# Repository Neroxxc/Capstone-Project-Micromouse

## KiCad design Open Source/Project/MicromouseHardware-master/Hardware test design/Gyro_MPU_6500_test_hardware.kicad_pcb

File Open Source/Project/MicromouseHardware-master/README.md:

# MicromouseHardware
This is the Hardware design for my micromouse. I will be participating in the UC San Diego's IEEE Micromouse competition 

 More images can be found [here](https://github.com/yyekalo/MicromouseHardware/tree/master/Media%20Files)

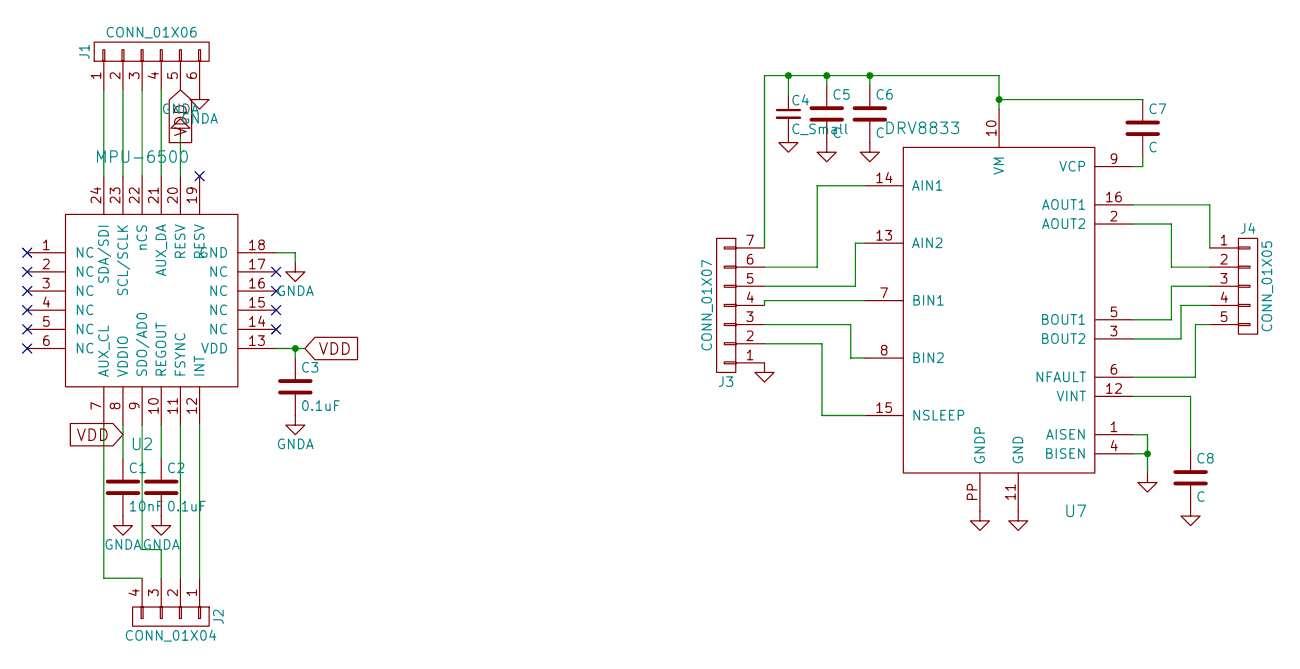
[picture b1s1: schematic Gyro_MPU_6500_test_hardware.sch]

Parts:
C1: 10nF; C_0603
C2, C3: 0.1uF; C_0603
C4: C_Small; CP_Radial_D5.0mm_P2.00mm
C5, C6, C7, C8: C; C_0603
J1: CONN_01X06; JST_EH_B06B-EH-A_06x2.50mm_Straight
J2: CONN_01X04; HDRV4W25P254_4X1_1016X254H1135
J3: CONN_01X07; JST_EH_B07B-EH-A_07x2.50mm_Straight
J4: CONN_01X05; JST_EH_B05B-EH-A_05x2.50mm_Straight
U2: MPU-6500
U7: DRV8833

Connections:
GNDA: C1.2, C2.2, C3.2, C4.2, C5.2, C6.2, C8.2, J1.6, J3.1, U2.18 (GND), U2.20 (RESV), U7.1 (AISEN), U7.4 (BISEN), U7.11 (GND), U7.PP (GNDP)
unnamed: C2.1, U2.10 (REGOUT)
unnamed: C4.1, C5.1, C6.1, C7.1, J3.7, U7.10 (VM)
unnamed: C7.2, U7.9 (VCP)
unnamed: C8.1, U7.12 (VINT)
unnamed: J1.1, U2.24 (SDA/SDI)
unnamed: J1.2, U2.23 (SCL/SCLK)
unnamed: J1.3, U2.22 (nCS)
unnamed: J1.4, U2.21 (AUX_DA)
unnamed: J2.1, U2.12 (INT)
unnamed: J2.2, U2.11 (FSYNC)
unnamed: J2.3, U2.9 (SDO/AD0)
unnamed: J2.4, U2.7 (AUX_CL)
unnamed: J3.2, U7.15 (NSLEEP)
unnamed: J3.3, U7.8 (BIN2)
unnamed: J3.4, U7.7 (BIN1)
unnamed: J3.5, U7.13 (AIN2)
unnamed: J3.6, U7.14 (AIN1)
unnamed: J4.1, U7.16 (AOUT1)
unnamed: J4.2, U7.2 (AOUT2)
unnamed: J4.3, U7.5 (BOUT1)
unnamed: J4.4, U7.3 (BOUT2)
unnamed: J4.5, U7.6 (NFAULT)
VDD: C1.1, C3.1, J1.5, U2.8 (VDDIO), U2.13 (VDD)

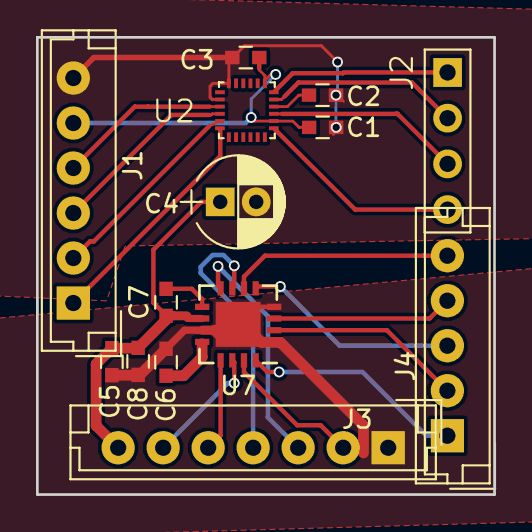
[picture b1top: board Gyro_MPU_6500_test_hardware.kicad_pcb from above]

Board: 2 copper layers, 25.4 x 25.4 mm, 14 parts (0 on the bottom side), 24 nets.

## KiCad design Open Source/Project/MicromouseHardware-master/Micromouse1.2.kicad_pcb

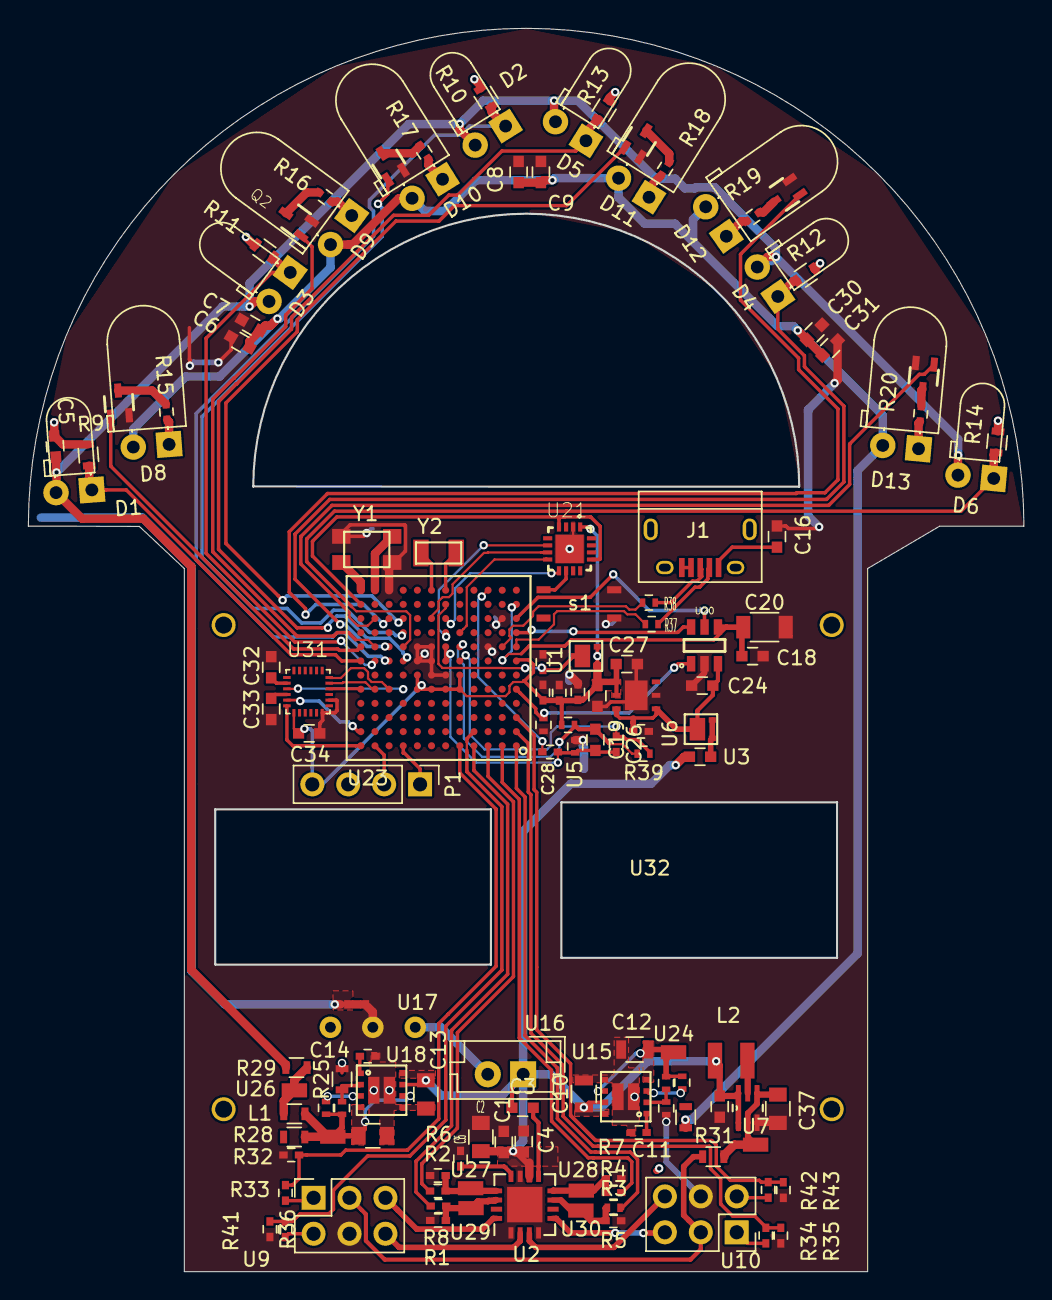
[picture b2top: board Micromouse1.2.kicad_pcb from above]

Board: 2 copper layers, 70.4 x 87.9 mm, 132 parts (0 on the bottom side), 102 nets.

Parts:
C1: 100uF; C_0603
C2, C13, C37: 10uF; C_0805
C3: 0.01uF; C_0603
C4, C5, C33: 0.1uF; C_0603
C6, C7, C8, C9, C30, C31, C34: C; C_0603
C10: 10uF; R_0805
C11, C14: 3300pF; C_0402
C12: 22uF; R_0805
C15: 22uF; C_0805
C16, C18, C19, C24, C27, C29: 2.2uF; C_0603
C17, C21, C22, C26, C28: 0.1uF; C_0402
C20: 100uF; C_1206
C23, C25: 10nF; C_0402
C32: 10nF; C_0603
C35: 2.2uF; C_0402
C36: 10uF; C_0603
D1, D2, D3, D4, D5, D6: IR_Reciver
D8, D9, D10, D11, D12, D13: IR_Emitter
J1: USB_B; USB_Micro-B
L1: L; L_0603
L2: 4.7uH; Neosid_Inductor_SM-NE29_SMD1008
P1: CONN_01X4; Socket_Strip_Straight_1x04_Pitch2.54mm
Q1, Q2, Q3, Q4, Q5, Q6: Q_NMOS_DGS; DMG1012UW
R1, R2, R4: 0; C_0402
R3: 0; R_0402
R5, R6, R7, R8: 47k; C_0402
R9, R10, R11, R12, R13, R14: 1.8k; R_0603
R15, R16, R17, R18, R19, R20: 0.75; C_0402
R21: 150K; R_0402
R22, R26: 10k; R_0402
R23: 226K; R_0402
R24, R28, R29, R31: 0; R_0603
R25: 180k; R_0603
R27: 562k; R_0402
R32, R33, R34, R35, R36, R41, R42, R43: R; C_0402
R37, R38: 33; R_0402
R39: 470; R_0402
R40: 100k; R_0402
U1, U6: BAT54C; PMEG4010_DIODE
U2: DRV8833
U3: 120; C_0603
U4: TPS61222DCK
U5, U14: 600; R_0402
U7, U24, U25, U26, U27, U28, U29, U30: Test_Point
U9, U10: CONN_02X03; Motors_connectors
U15, U18: LMZ21701
U16: JST_Connector
U17: Switch_micromouse; Switch_battery
U19: splitter; spliter
U20: TPD3S014
U21: MKL02Z32VFG4
U22: LP38691
U23: MK66FX1M0; Microcontroller
U31: MPU-6500
U32: Motor_mount
Y1: Crystal_16MHz; 16Mhz_crystal
Y2: 32.768MHz; 32.768_CRYSTAL
s1: Switch; Switch_teensy

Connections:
/Micro controller/D+: J1.3, R38.2
/Micro controller/D-: J1.2, R37.2
/Micro controller/USB0_+: R37.1, U23.H1
/Micro controller/USB0_-: R38.1, U23.H2
FSYNC: U23.B12, U31.11
GNDA: C5.2, R9.2, R10.2, R11.2, R12.2, R13.2, R14.2, U19.2
GNDD: C1.2, C2.2, C4.2, C6.2, C7.2, C8.2, C9.2, C10.2, C11.2, C12.2, C13.2, C14.2, C15.2, C16.2, C17.2, C18.2, C20.2, C21.2, C22.2, C23.2, C24.2, C25.2, C27.2, C29.2, C30.2, C31.2, C32.2, C33.2, C34.2, C35.2, C36.2, C37.2, Q1.3, Q2.3, Q3.3, Q4.3, Q5.3, Q6.3, R5.2, R6.1, R7.2, R8.1, R21.2, R25.2, R32.2, R35.2, R36.2, R40.2, R43.2, U2.1, U2.4, U2.11, U2.PP, U4.3, U5.1, U9.4, U10.4, U15.5, U17.2, U18.5, U19.1, U20.2, U21.2, U21.PAD, U22.2, U23.F6, U23.F7, U23.G7, U23.G8, U23.H3, U23.H7, U23.H8, U23.K2, U23.M10, U31.18, U31.20, Y1.2, s1.2
INT: U23.A12, U31.12
LD_EMITTER: Q3.2, U23.J9
LD_RECEIVER: D2.1, R10.1, U23.G10
LF_EMITTER: Q1.2, U23.H12
LF_RECEIVER: D3.1, R11.1, U23.G11
L_CH_A: R42.2, R43.1, U23.C1
L_CH_B: R34.2, R35.1, U23.B1
L_EMITTER: Q2.2, U23.H11
L_PWM_A: R3.2, U23.A1
L_PWM_B: R4.2, U23.A2
L_RECEIVER: D1.1, R9.1, U23.G12
MCUv: C22.1, C23.1, C25.1, C27.1, C29.1, C34.1, P1.4, U1.1, U1.2, U14.1, U21.1, U22.4, U22.5, U23.E5, U23.E6, U23.E7, U23.E8, U23.F5, U23.F8, U23.G1, U31.13
unnamed: C3.2, U2.9
unnamed: C11.1, U15.1
unnamed: C12.1, R22.2, R23.1, R24.2, U15.4, U15.6, U24.1
unnamed: C14.1, U18.1
unnamed: C15.1, L1.1, R26.2, R27.1, R28.2, U18.4, U18.6, U25.1
unnamed: C16.1, J1.1
unnamed: C17.1, U1.3, U23.L6
unnamed: C18.1, C20.1, U20.4, U23.G2, U23.L1
unnamed: C19.1, R39.2, U14.2, U23.H5
unnamed: C19.2, C26.2, C28.2, U5.2, U23.G6, U23.H6
unnamed: C21.1, C24.1, U6.3, U20.3, U22.1, U22.6
unnamed: C26.1, R39.1, U23.G5
unnamed: C28.1, U23.M3
unnamed: C32.1, U31.8
unnamed: C33.1, U31.10
unnamed: C35.1, U2.12
unnamed: C37.1, R31.2, U4.2, U4.4, U7.1
unnamed: D8.1, R15.2
unnamed: D9.1, R16.2
unnamed: D10.1, R17.2
unnamed: D11.1, R18.2
unnamed: D12.1, R19.2
unnamed: D13.1, R20.2
unnamed: J1.4, J1.5
unnamed: L1.2, R29.1, U26.1
unnamed: L2.2, U4.5
unnamed: Q1.1, R15.1
unnamed: Q2.1, R16.1
unnamed: Q3.1, R17.1
unnamed: Q4.1, R18.1
unnamed: Q5.1, R19.1
unnamed: Q6.1, R20.1
unnamed: R1.1, R8.2, U2.14, U29.1
unnamed: R2.1, R6.2, U2.13, U27.1
unnamed: R3.1, R5.1, U2.7, U30.1
unnamed: R4.1, R7.1, U2.8, U28.1
unnamed: R21.1, R23.2, U15.2
unnamed: R22.1, U15.3
unnamed: R25.1, R27.2, U18.2
unnamed: R26.1, U18.3
unnamed: R33.1, U9.1
unnamed: R34.1, U10.1
unnamed: R40.1, U20.1, U23.E1
unnamed: R41.1, U9.2
unnamed: R42.1, U10.2
unnamed: U2.2, U9.6
unnamed: U2.16, U9.5
unnamed: U3.2, U6.1, U6.2
unnamed: U2.5, U10.5
unnamed: U2.3, U10.6
unnamed: U16.2, U17.1
unnamed: U20.5, U23.K1
unnamed: U20.6, U23.J1
unnamed: U21.6, U23.J6
unnamed: U21.7, U23.K7
unnamed: U21.8, U23.J5
unnamed: U21.9, U23.K6
unnamed: U21.10, s1.1
unnamed: U21.4, U21.13, U23.L12
unnamed: U23.M6, Y2.2
unnamed: U23.M7, Y2.1
unnamed: U23.M11, Y1.3
unnamed: U23.M12, Y1.1
RD_EMITTER: Q4.2, U23.K9
RD_RECEIVER: D5.1, R13.1, U23.G9
RF_EMITTER: Q6.2, U23.K11
RF_RECEIVER: D4.1, R12.1, U23.H10
RX: P1.1, U23.A9
R_CH_A: R32.1, R33.2, U23.A5
R_CH_B: R36.1, R41.2, U23.B4
R_EMITTER: Q5.2, U23.K10
R_PWM_A: R1.2, U23.A4
R_PWM_B: R2.2, U23.A3
R_RECEIVER: D6.1, R14.1, U23.H9
SCLK: U23.E11, U31.23
SDI: U23.E10, U31.24
SDO: U23.E9, U31.9
TX: P1.2, U23.A11
V2: C6.1, C7.1, C8.1, C9.1, C30.1, C31.1, D8.2, D9.2, D10.2, D11.2, D12.2, D13.2, R24.1
V5: R31.1, U9.3, U10.3
VA3.3: C5.1, D1.2, D2.2, D3.2, D4.2, D5.2, D6.2, R29.2
V_BAT: C1.1, C2.1, C3.1, C4.1, C10.1, C13.1, C36.1, L2.1, U2.10, U3.1, U4.1, U4.6, U15.7, U15.8, U16.1, U18.7, U18.8
nCS: U23.E12, U31.22
